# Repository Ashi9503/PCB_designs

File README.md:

# PCB_designs
Test PCB designs in KiCaD

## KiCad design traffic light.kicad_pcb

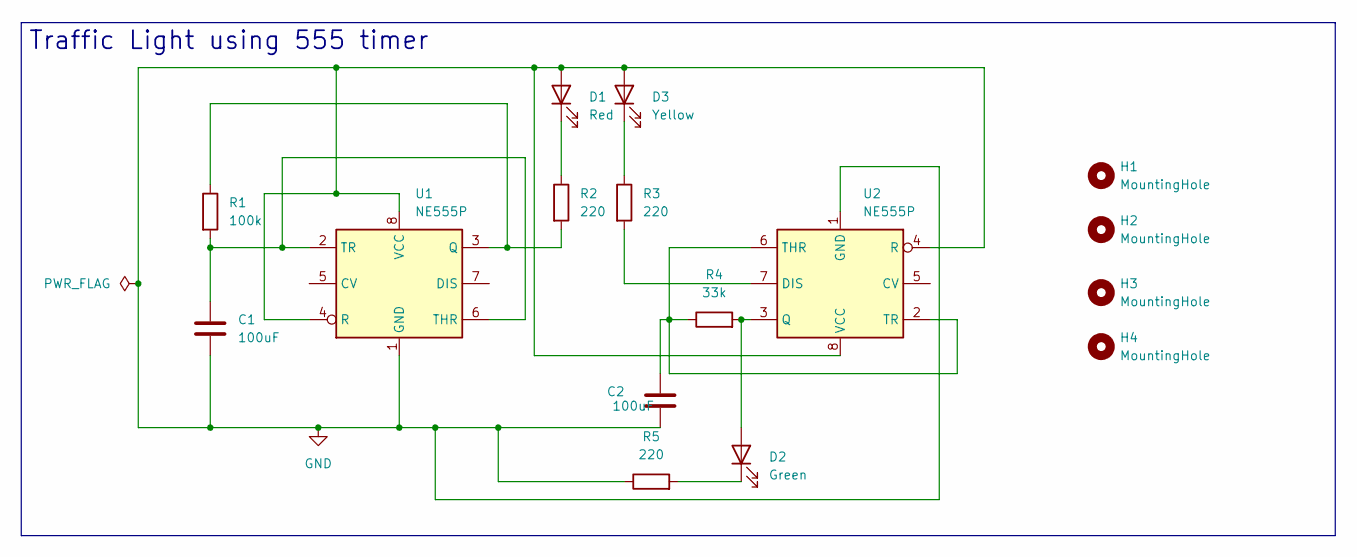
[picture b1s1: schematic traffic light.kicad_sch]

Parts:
C1, C2: 100uF; CP_Radial_D8.0mm_P3.50mm
D1: Red; LED_D3.0mm
D2: Green; LED_D3.0mm
D3: Yellow; LED_D3.0mm
H1, H2, H3, H4: MountingHole; MountingHole_2mm
R1: 100k; R_Axial_DIN0207_L6.3mm_D2.5mm_P5.08mm_Vertical
R2, R3, R5: 220; R_Axial_DIN0207_L6.3mm_D2.5mm_P5.08mm_Vertical
R4: 33k; R_Axial_DIN0207_L6.3mm_D2.5mm_P5.08mm_Vertical
U1, U2: NE555P; DIP-8_W7.62mm

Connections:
GND: C1.2, C2.2, D1.2 (A), D3.2 (A), R5.1, U1.1 (GND), U1.4 (R), U1.8 (VCC), U2.1 (GND), U2.4 (R), U2.8 (VCC)
unnamed: D1.1 (K), R2.1
unnamed: D2.2 (A), R4.2, U2.3 (Q)
unnamed: D2.1 (K), R5.2
unnamed: D3.1 (K), R3.1
unnamed: R1.1, R2.2, U1.3 (Q)
unnamed: C1.1, R1.2, U1.2 (TR), U1.6 (THR)
unnamed: R3.2, U2.7 (DIS)
unnamed: C2.1, R4.1, U2.2 (TR), U2.6 (THR)

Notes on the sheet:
Traffic Light using 555 timer

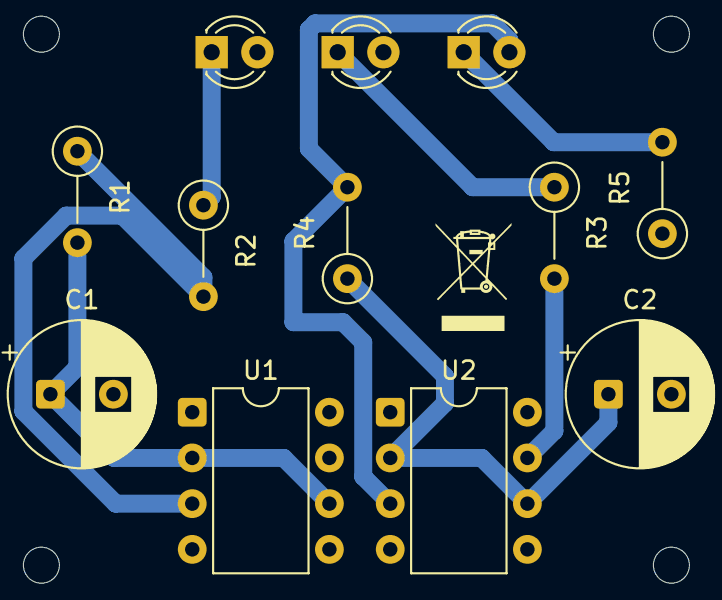
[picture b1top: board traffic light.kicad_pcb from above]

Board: 2 copper layers, 16 parts (0 on the bottom side), 9 nets.

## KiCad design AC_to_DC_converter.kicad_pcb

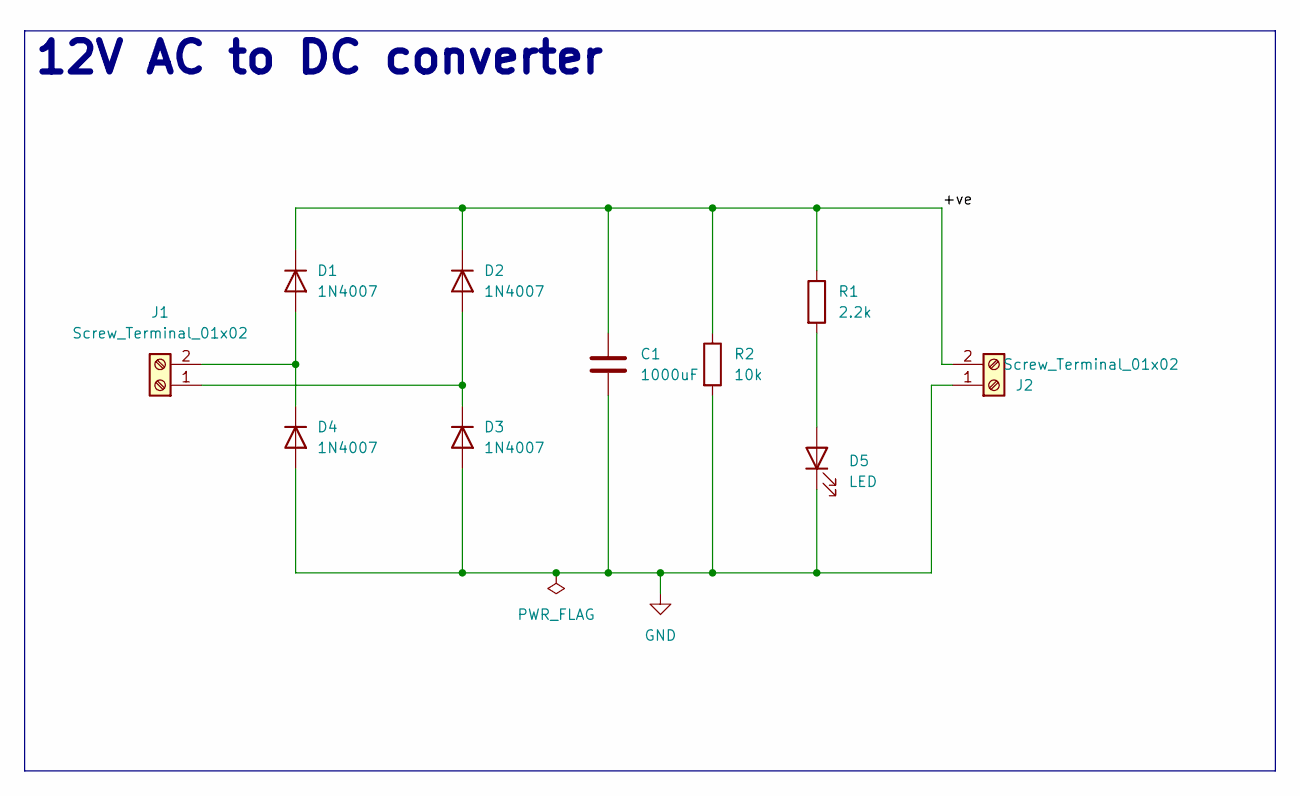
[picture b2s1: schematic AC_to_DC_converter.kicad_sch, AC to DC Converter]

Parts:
C1: 1000uF; CP_Radial_D8.0mm_P3.80mm
D1, D2, D3, D4: 1N4007; D_DO-41_SOD81_P10.16mm_Horizontal
D5: LED; LED_D5.0mm
J1, J2: Screw_Terminal_01x02; TerminalBlock_bornier-2_P5.08mm
R1: 2.2k; R_Axial_DIN0207_L6.3mm_D2.5mm_P7.62mm_Horizontal
R2: 10k; R_Axial_DIN0207_L6.3mm_D2.5mm_P7.62mm_Horizontal

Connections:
/+ve: C1.1, D1.1 (K), D2.1 (K), J2.2, R1.1, R2.1
GND: C1.2, D3.2 (A), D4.2 (A), D5.1 (K), J2.1, R2.2
unnamed: D1.2 (A), D4.1 (K), J1.2
unnamed: D2.2 (A), D3.1 (K), J1.1
unnamed: D5.2 (A), R1.2

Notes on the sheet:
12V AC to DC converter

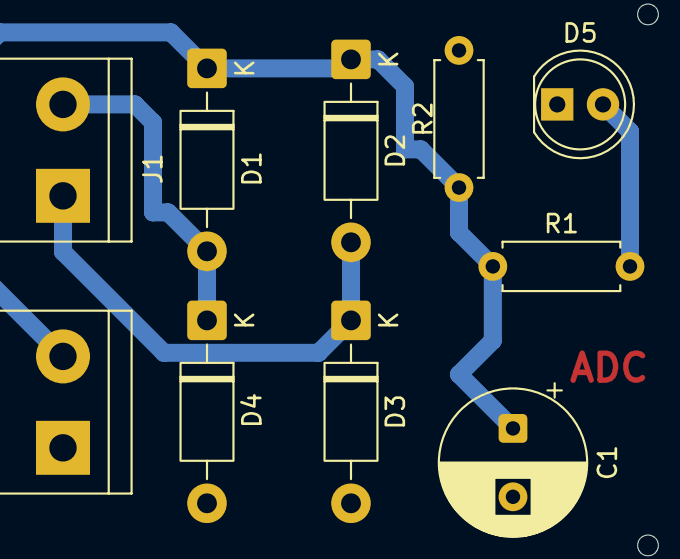
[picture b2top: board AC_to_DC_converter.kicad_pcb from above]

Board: 2 copper layers, 10 parts (0 on the bottom side), 5 nets.
